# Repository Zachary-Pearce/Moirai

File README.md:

<p align="center">

<br>

</p>

Moirai is a 3-Channel majority voter for redundant flight computer systems made with KiCad. It allows you to properly implement redundant systems in hobby rockets whether they be high power or low power.

## Installation
1. Clone the repository:

```bash
git clone https://github.com/Zachary-Pearce/Moirai
```

2. Open the folder in KiCad and confirm the local libraries have been imported.

## Usage
> [!WARNING]
> Rocketry is a dangerous hobby, you are using this device at your own risk, incorrect usage may result in unexpected behaviour.

Before deciding to get this PCB for yourself, I reccomend that you read the full manual present in the wiki.

If you are going to get this PCB cut, I would reccomend using [JLCPCB](https://jlcpcb.com/), when creating your Gerber and Drill files, please follow the [relevant guide](https://jlcpcb.com/help/catalog/180-PCB-Files-Preparation) for your version of KiCad.

## Contributing
1. Fork this repository
2. Clone your fork
3. Make your changes
4. Submit a pull request

Ensure that your pull request includes the following:
- What has changed?
- Why has it changed?
- Proof testing has been carried out to ensure your changes work.

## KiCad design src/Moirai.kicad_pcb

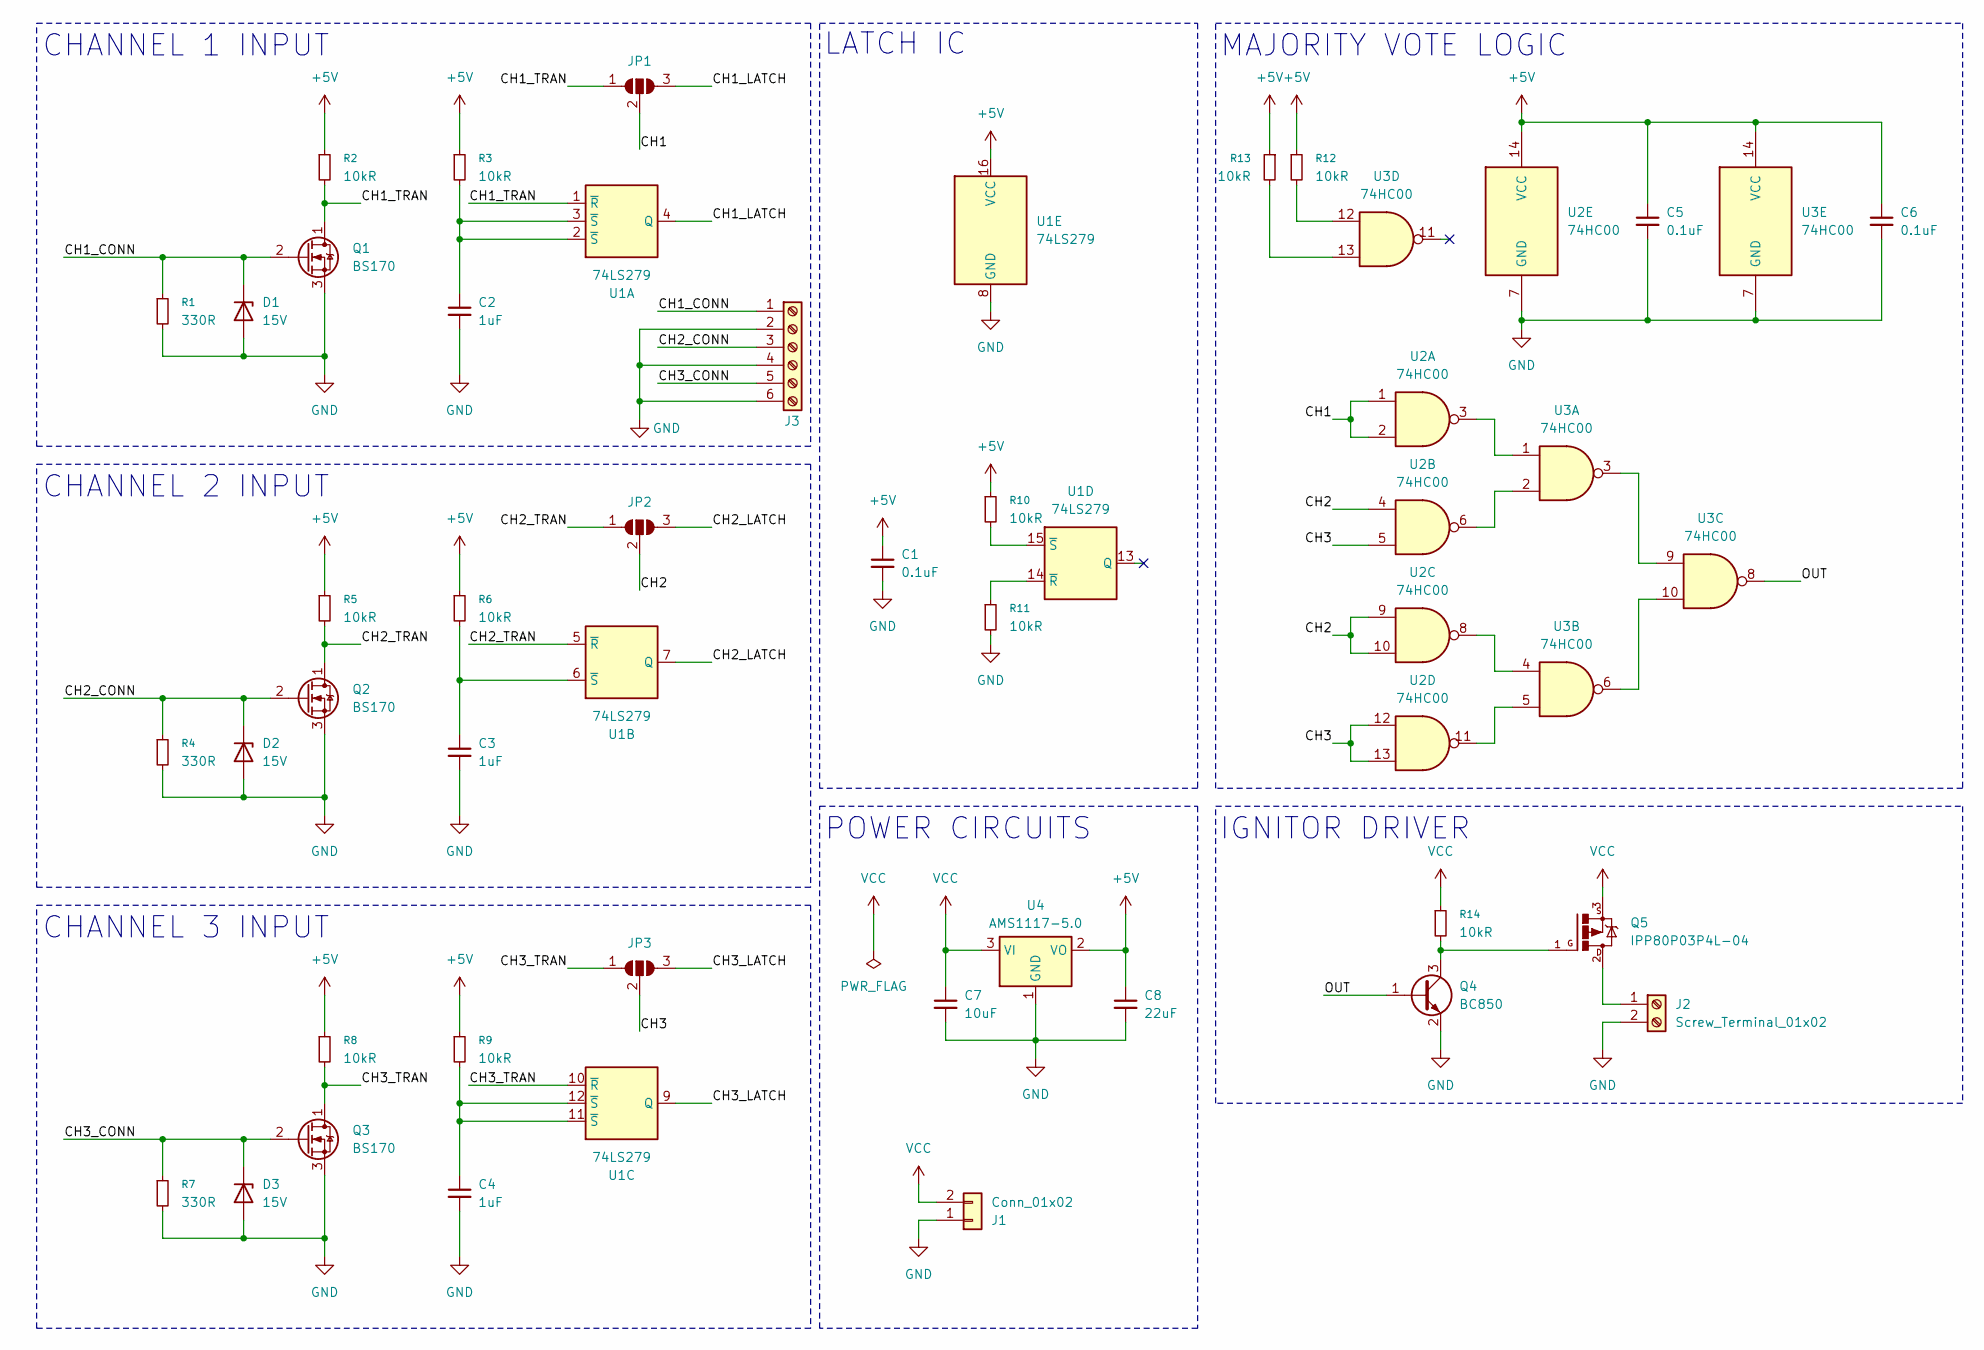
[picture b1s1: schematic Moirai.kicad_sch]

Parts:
C1, C5, C6: 0.1uF; C_0805_2012Metric
C2, C3, C4: 1uF; C_0805_2012Metric
C7: 10uF; C_0805_2012Metric
C8: 22uF; C_0805_2012Metric
D1, D2, D3: 15V; D_SMA
J1: Conn_01x02; AMASS_XT30U-M_1x02_P5.0mm_Vertical
J2: Screw_Terminal_01x02; TerminalBlock_WAGO_236-402_1x02_P5.00mm_45Degree
J3: Screw_Terminal_01x06; TerminalBlock_WAGO_236-406_1x06_P5.00mm_45Degree
JP1, JP2, JP3: SolderJumper_3_Open; SolderJumper-3_P2.0mm_Open_TrianglePad1.0x1.5mm
Q1, Q2, Q3: BS170; TO-92_Inline
Q4: BC850; SOT-23
Q5: IPP80P03P4L-04; TO-220-3_Vertical
R1, R4, R7: 330R; R_0805_2012Metric
R2, R3, R5, R6, R8, R9, R10, R11, R12, R13, R14: 10kR; R_0805_2012Metric
U1: 74LS279; DIP-16_W7.62mm
U2, U3: 74HC00; DIP-14_W7.62mm
U4: AMS1117-5.0; SOT-223-3_TabPin2

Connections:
+5V: C1.1, C5.1, C6.1, C8.1, R2.1, R3.1, R5.1, R6.1, R8.1, R9.1, R10.1, R12.1, R13.1, U1.16 (VCC), U2.14 (VCC), U3.14 (VCC), U4.2 (VO)
/CH1: JP1.2 (C), U2.1, U2.2
/CH1_CONN: D1.1 (K), J3.1, Q1.2 (G), R1.1
/CH1_LATCH: JP1.3 (B), U1.4 (Q)
/CH1_TRAN: JP1.1 (A), Q1.1 (D), R2.2, U1.1 (~R)
/CH2: JP2.2 (C), U2.4, U2.9, U2.10
/CH2_CONN: D2.1 (K), J3.3, Q2.2 (G), R4.1
/CH2_LATCH: JP2.3 (B), U1.7 (Q)
/CH2_TRAN: JP2.1 (A), Q2.1 (D), R5.2, U1.5 (~R)
/CH3: JP3.2 (C), U2.5, U2.12, U2.13
/CH3_CONN: D3.1 (K), J3.5, Q3.2 (G), R7.1
/CH3_LATCH: JP3.3 (B), U1.9 (Q)
/CH3_TRAN: JP3.1 (A), Q3.1 (D), R8.2, U1.10 (~R)
/OUT: Q4.1 (B), U3.8
GND: C1.2, C2.2, C3.2, C4.2, C5.2, C6.2, C7.2, C8.2, D1.2 (A), D2.2 (A), D3.2 (A), J1.1, J2.2, J3.2, J3.4, J3.6, Q1.3 (S), Q2.3 (S), Q3.3 (S), Q4.2 (E), R1.2, R4.2, R7.2, R11.2, U1.8 (GND), U2.7 (GND), U3.7 (GND), U4.1 (GND)
unnamed: C2.1, R3.2, U1.2 (~S), U1.3 (~S)
unnamed: C4.1, R9.2, U1.11 (~S), U1.12 (~S)
unnamed: J2.1, Q5.2
unnamed: Q4.3 (C), Q5.1, R14.2
unnamed: R12.2, U3.12
unnamed: R13.2, U3.13
unnamed: C3.1, R6.2, U1.6 (~S)
unnamed: R11.1, U1.14 (~R)
unnamed: R10.2, U1.15 (~S)
unnamed: U2.3, U3.1
unnamed: U2.6, U3.2
unnamed: U2.8, U3.4
unnamed: U2.11, U3.5
unnamed: U3.3, U3.9
unnamed: U3.6, U3.10
VCC: C7.1, J1.2, Q5.3, R14.1, U4.3 (VI)

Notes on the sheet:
IGNITOR DRIVER
MAJORITY VOTE LOGIC
CHANNEL 3 INPUT
CHANNEL 1 INPUT
CHANNEL 2 INPUT
LATCH IC
POWER CIRCUITS

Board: 2 copper layers, 40 parts (0 on the bottom side), 31 nets, no tracks yet.

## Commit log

2025-07-09 Create .mailmap
    Initial commit
2025-07-09 Added logo and structure
2025-07-09 logo sizing
2025-07-10 updated schematic
2025-07-19 relocated libraries
2025-07-19 changed logo to images
2025-07-19 uploaded code of conduct
2025-07-19 fixed IPP80P symbol
2025-07-20 PCB design
2025-07-20 PCB update
